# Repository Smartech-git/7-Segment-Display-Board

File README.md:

# 7-Segment-Display-Board
Designed with KiCad V6

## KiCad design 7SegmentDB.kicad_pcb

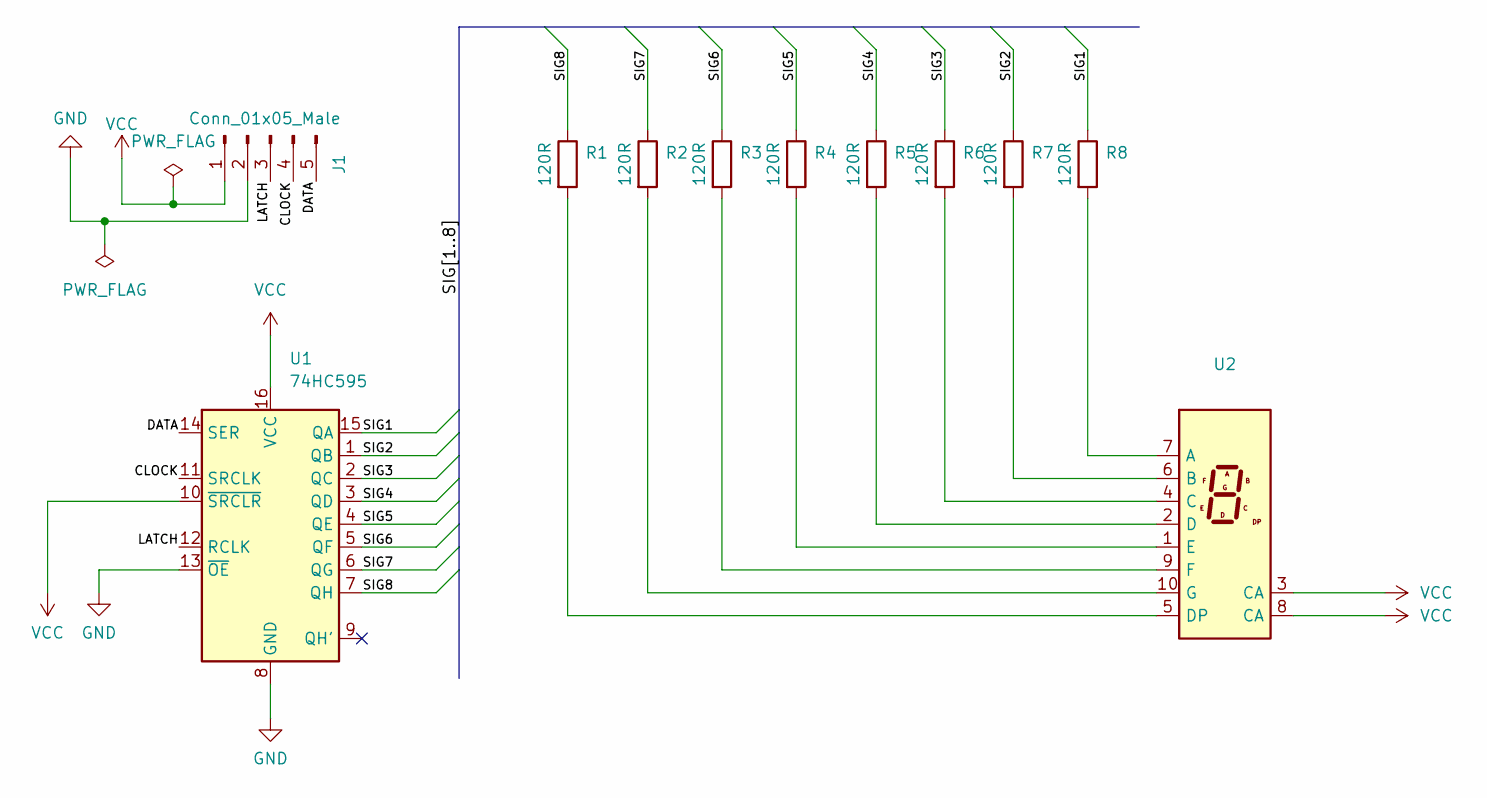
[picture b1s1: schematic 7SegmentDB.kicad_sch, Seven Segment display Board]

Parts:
J1: Conn_01x05_Male; PinHeader_1x05_P2.54mm_Vertical
R1, R2, R3, R4, R5, R6, R7, R8: 120R; R_Axial_DIN0207_L6.3mm_D2.5mm_P10.16mm_Horizontal
U1: 74HC595; DIP-16_W7.62mm
U2: (no value)

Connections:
/CLOCK: J1.4, U1.11 (SRCLK)
/DATA: J1.5, U1.14 (SER)
/LATCH: J1.3, U1.12 (RCLK)
/SIG1: R8.1, U1.15 (QA)
/SIG2: R7.1, U1.1 (QB)
/SIG3: R6.1, U1.2 (QC)
/SIG4: R5.1, U1.3 (QD)
/SIG5: R4.1, U1.4 (QE)
/SIG6: R3.1, U1.5 (QF)
/SIG7: R2.1, U1.6 (QG)
/SIG8: R1.1, U1.7 (QH)
GND: J1.2, U1.8 (GND), U1.13 (~OE)
unnamed: R1.2, U2.5 (DP)
unnamed: R2.2, U2.10 (G)
unnamed: R3.2, U2.9 (F)
unnamed: R4.2, U2.1 (E)
unnamed: R5.2, U2.2 (D)
unnamed: R6.2, U2.4 (C)
unnamed: R7.2, U2.6 (B)
unnamed: R8.2, U2.7 (A)
VCC: J1.1, U1.10 (~SRCLR), U1.16 (VCC), U2.3 (CA), U2.8 (CA)

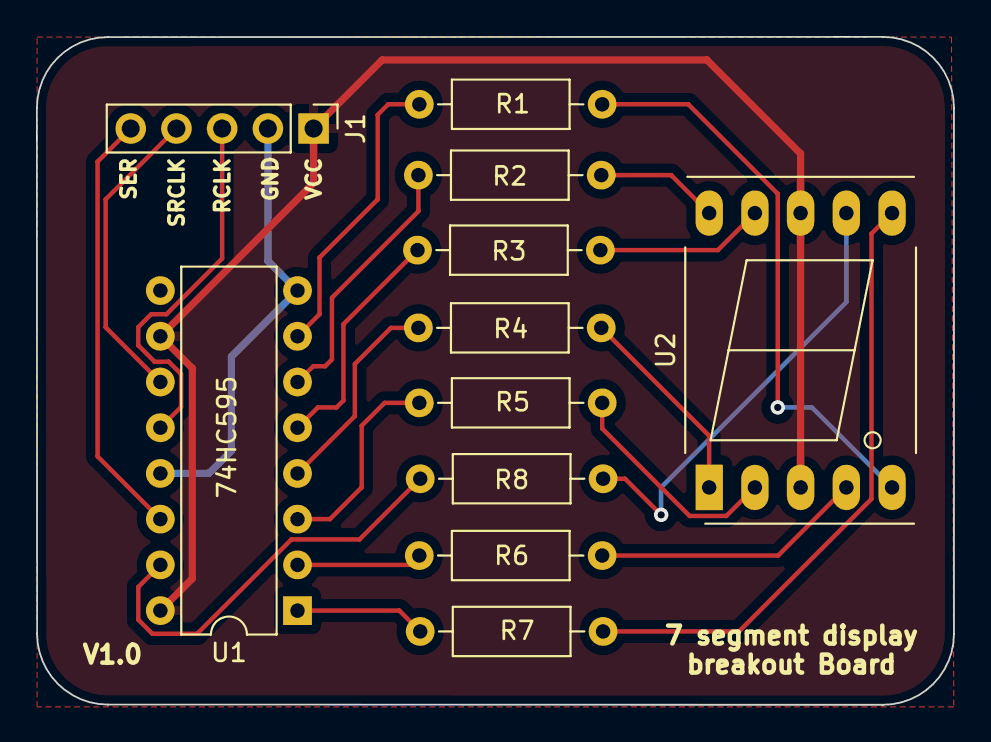
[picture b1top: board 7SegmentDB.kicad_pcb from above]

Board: 2 copper layers, 50.9 x 37.1 mm, 11 parts (0 on the bottom side), 21 nets.

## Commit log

2022-06-29 Create gerber
